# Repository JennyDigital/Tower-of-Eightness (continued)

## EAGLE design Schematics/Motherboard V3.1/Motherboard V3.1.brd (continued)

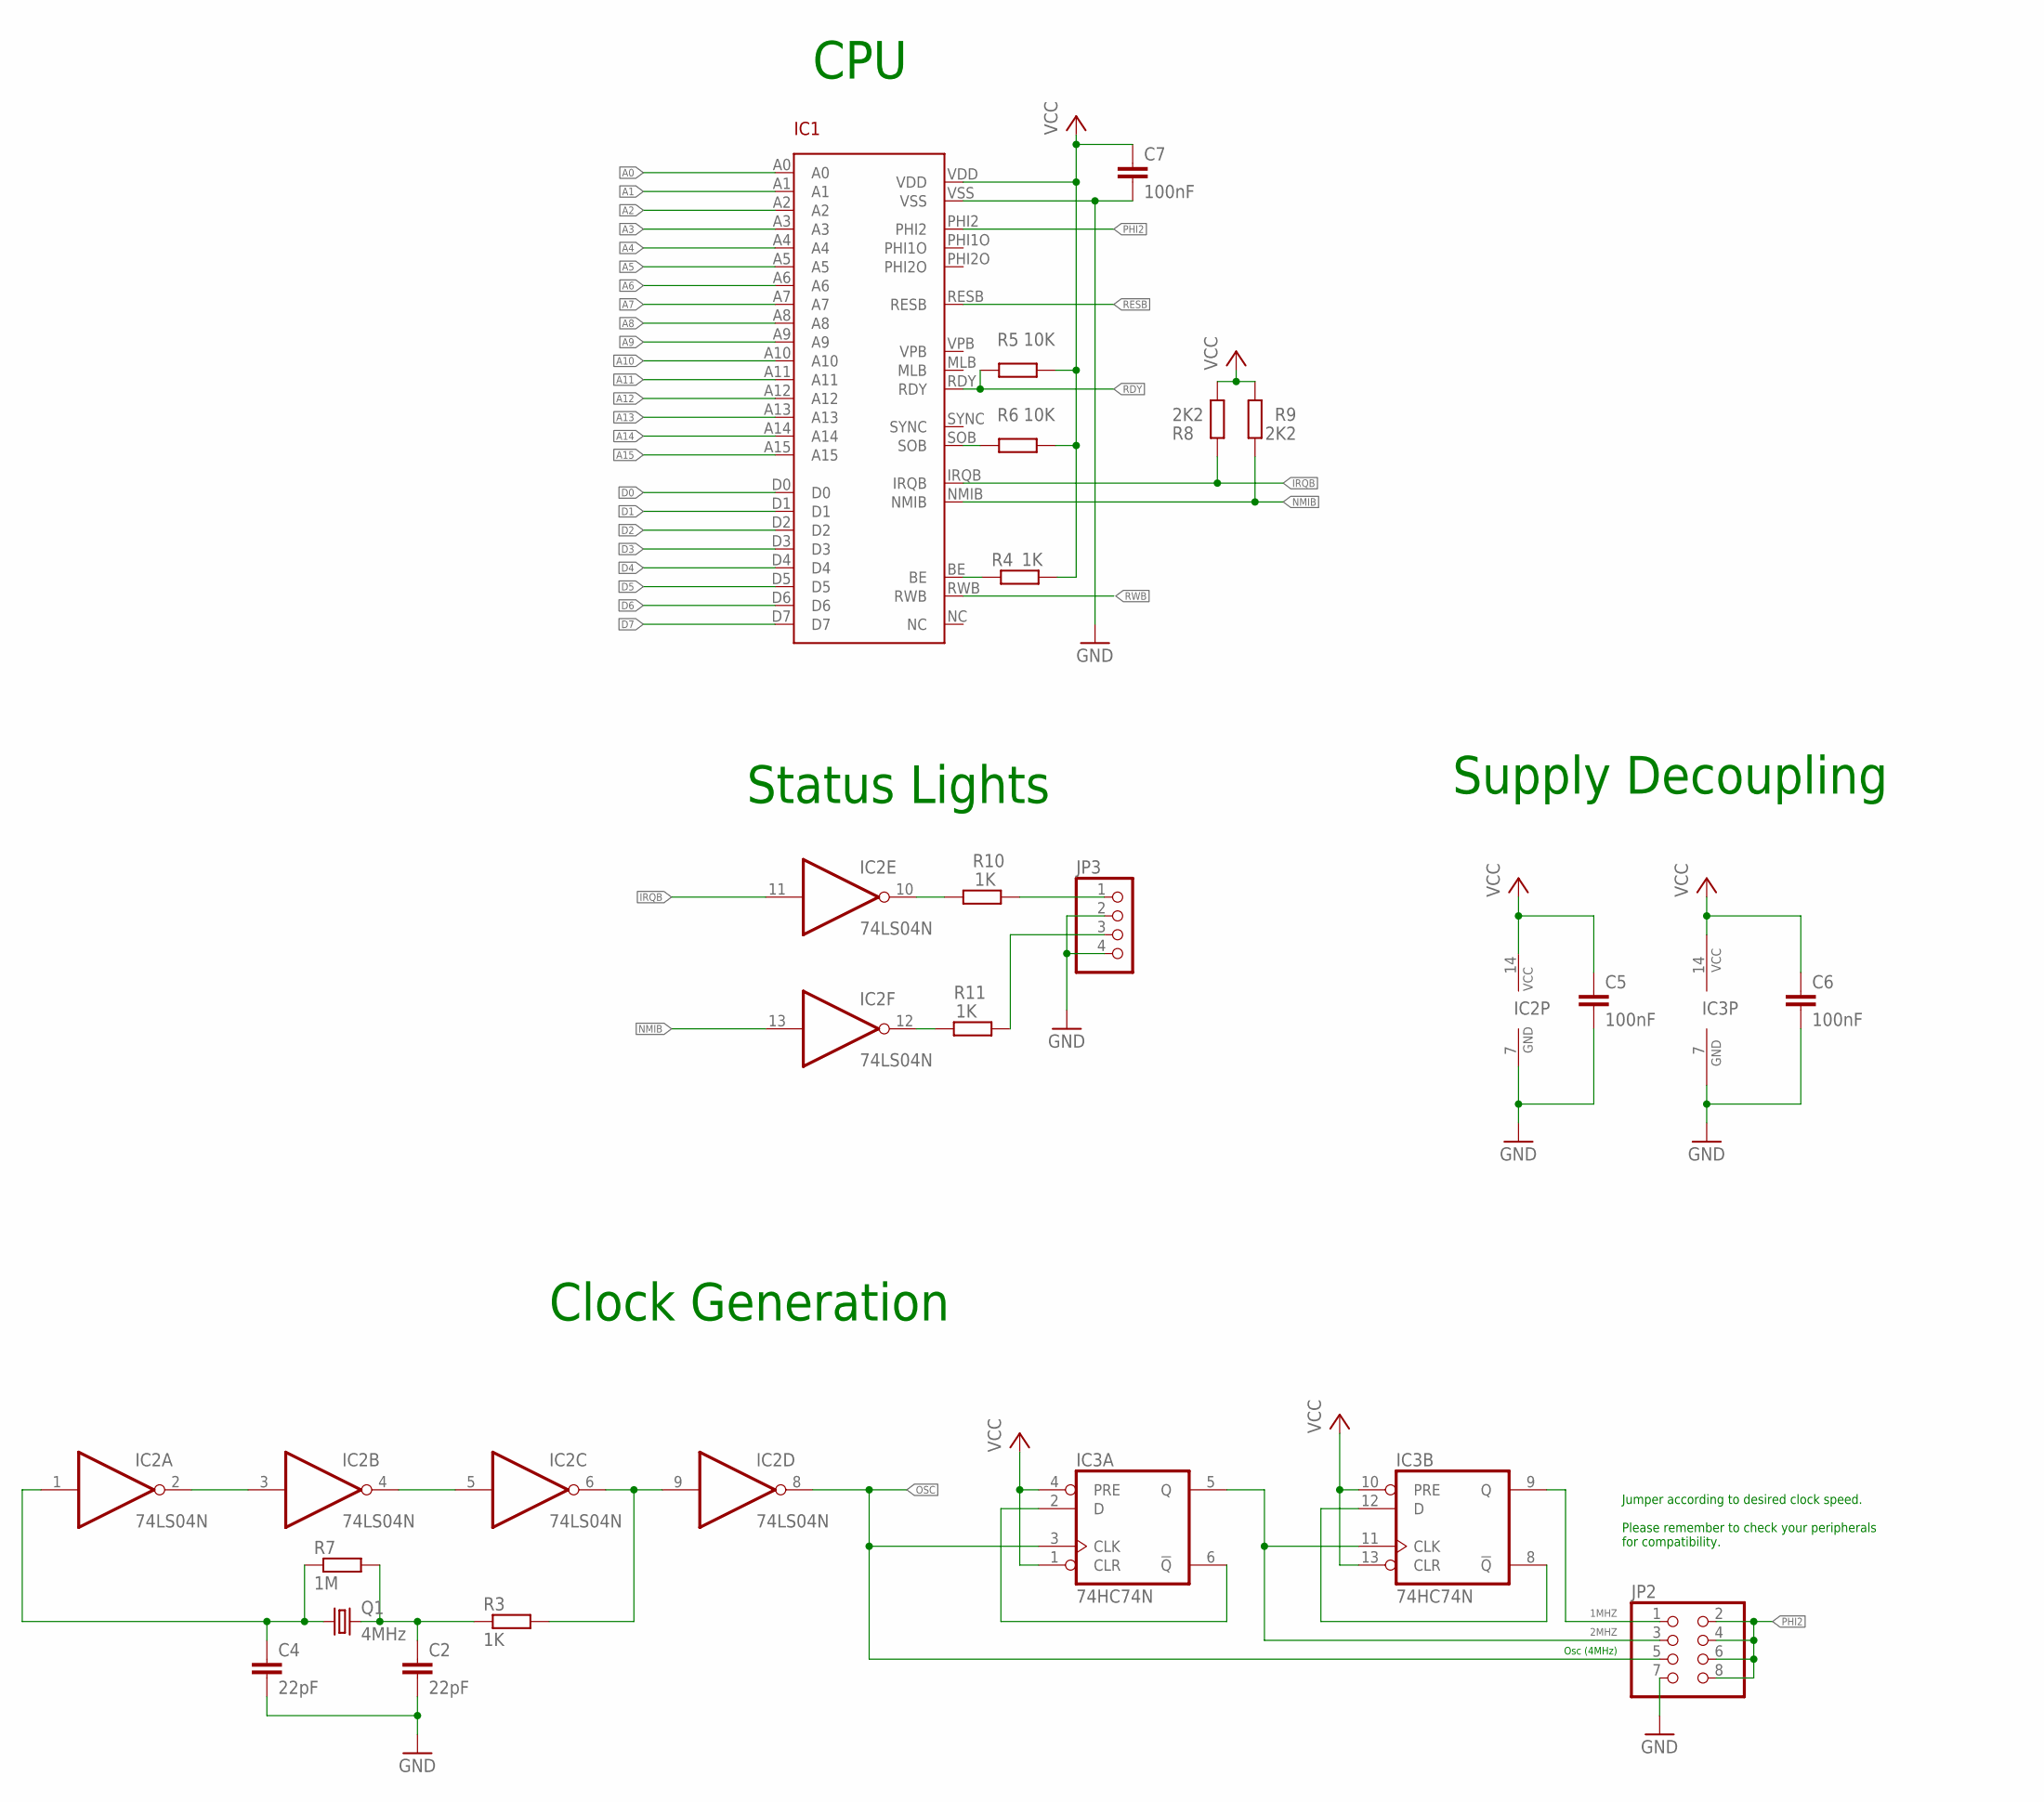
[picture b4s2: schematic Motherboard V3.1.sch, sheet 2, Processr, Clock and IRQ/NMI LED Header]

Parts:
C2, C4: 22pF; C025-025X050
C5, C6, C7: 100nF; C050-025X075
IC1: W65C02S-DIP; DIP40
IC2: 74LS04N; DIL14
IC3: 74HC74N; DIL14
JP2: PINHD-2X4; 2X04
JP3: PINHD-1X4; 1X04
Q1: 4MHz; HC49/S
R3, R10, R11: 1K; 0207/2V
R4: 1K; 0207/10
R5: 10K; 0207/2V
R6: 10K; 0207/10
R7: 1M; 0207/2V
R8, R9: 2K2; 0207/2V

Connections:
1MHZ: IC3.9 (Q), JP2.1
2MHZ: IC3.5 (Q), IC3.11 (CLK), JP2.3
A0: IC1.A0; also elsewhere on the board
A1: IC1.A1; also elsewhere on the board
A2: IC1.A2; also elsewhere on the board
A3: IC1.A3; also elsewhere on the board
A4: IC1.A4; also elsewhere on the board
A5: IC1.A5; also elsewhere on the board
A6: IC1.A6; also elsewhere on the board
A7: IC1.A7; also elsewhere on the board
A8: IC1.A8; also elsewhere on the board
A9: IC1.A9; also elsewhere on the board
A10: IC1.A10; also elsewhere on the board
A11: IC1.A11; also elsewhere on the board
A12: IC1.A12; also elsewhere on the board
A13: IC1.A13; also elsewhere on the board
A14: IC1.A14; also elsewhere on the board
A15: IC1.A15; also elsewhere on the board
D0: IC1.D0; also elsewhere on the board
D1: IC1.D1; also elsewhere on the board
D2: IC1.D2; also elsewhere on the board
D3: IC1.D3; also elsewhere on the board
D4: IC1.D4; also elsewhere on the board
D5: IC1.D5; also elsewhere on the board
D6: IC1.D6; also elsewhere on the board
D7: IC1.D7; also elsewhere on the board
GND: C2.2, C4.2, C5.2, C6.2, C7.2, IC1.VSS, IC2.7 (GND), IC3.7 (GND), JP2.7, JP3.2, JP3.4; also elsewhere on the board
IRQB: IC1.IRQB, IC2.11 (I), R8.1; also elsewhere on the board
IRQ_LED: JP3.1, R10.2
IRQ_SIG: IC2.10 (O), R10.1
unnamed: IC2.4 (O), IC2.5 (I)
unnamed: IC2.6 (O), IC2.9 (I), R3.2
unnamed: C2.1, Q1.2, R3.1, R7.2
unnamed: C4.1, IC2.1 (I), Q1.1, R7.1
unnamed: IC3.2 (D), IC3.6 (!Q)
unnamed: IC2.2 (O), IC2.3 (I)
unnamed: IC3.8 (!Q), IC3.12 (D)
unnamed: IC1.BE, R4.1
unnamed: IC1.SOB, R6.1
NMIB: IC1.NMIB, IC2.13 (I), R9.1; also elsewhere on the board
NMI_LED: JP3.3, R11.2
NMI_SIG: IC2.12 (O), R11.1
OSC: IC2.8 (O), IC3.3 (CLK), JP2.5; also elsewhere on the board
PHI2: IC1.PHI2, JP2.2, JP2.4, JP2.6, JP2.8; also elsewhere on the board
RDY: IC1.RDY, R5.1; also elsewhere on the board
RESB: IC1.RESB; also elsewhere on the board
RWB: IC1.RWB; also elsewhere on the board
VCC: C5.1, C6.1, C7.1, IC1.VDD, IC2.14 (VCC), IC3.1 (CLR), IC3.4 (PRE), IC3.10 (PRE), IC3.13 (CLR), IC3.14 (VCC), R4.2, R5.2, R6.2, R8.2, R9.2; also elsewhere on the board

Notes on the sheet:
CPU
Clock Generation
Status Lights
Supply Decoupling
Jumper according to desired clock speed. Please remember to check your peripherals for compatibility.
Osc (4MHz)

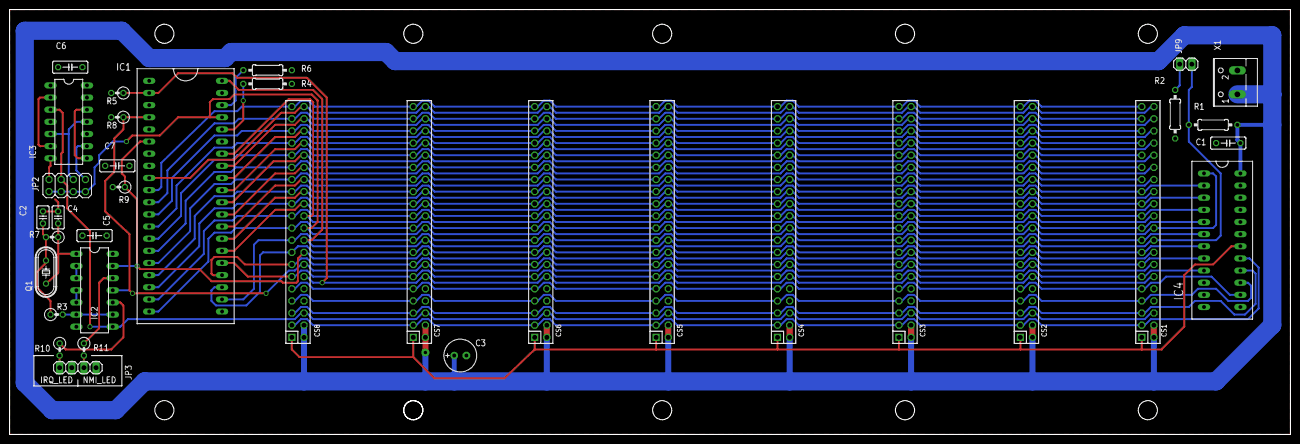
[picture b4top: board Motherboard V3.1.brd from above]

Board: 2 copper layers, 268.0 x 88.9 mm, 35 parts (0 on the bottom side), 54 nets.

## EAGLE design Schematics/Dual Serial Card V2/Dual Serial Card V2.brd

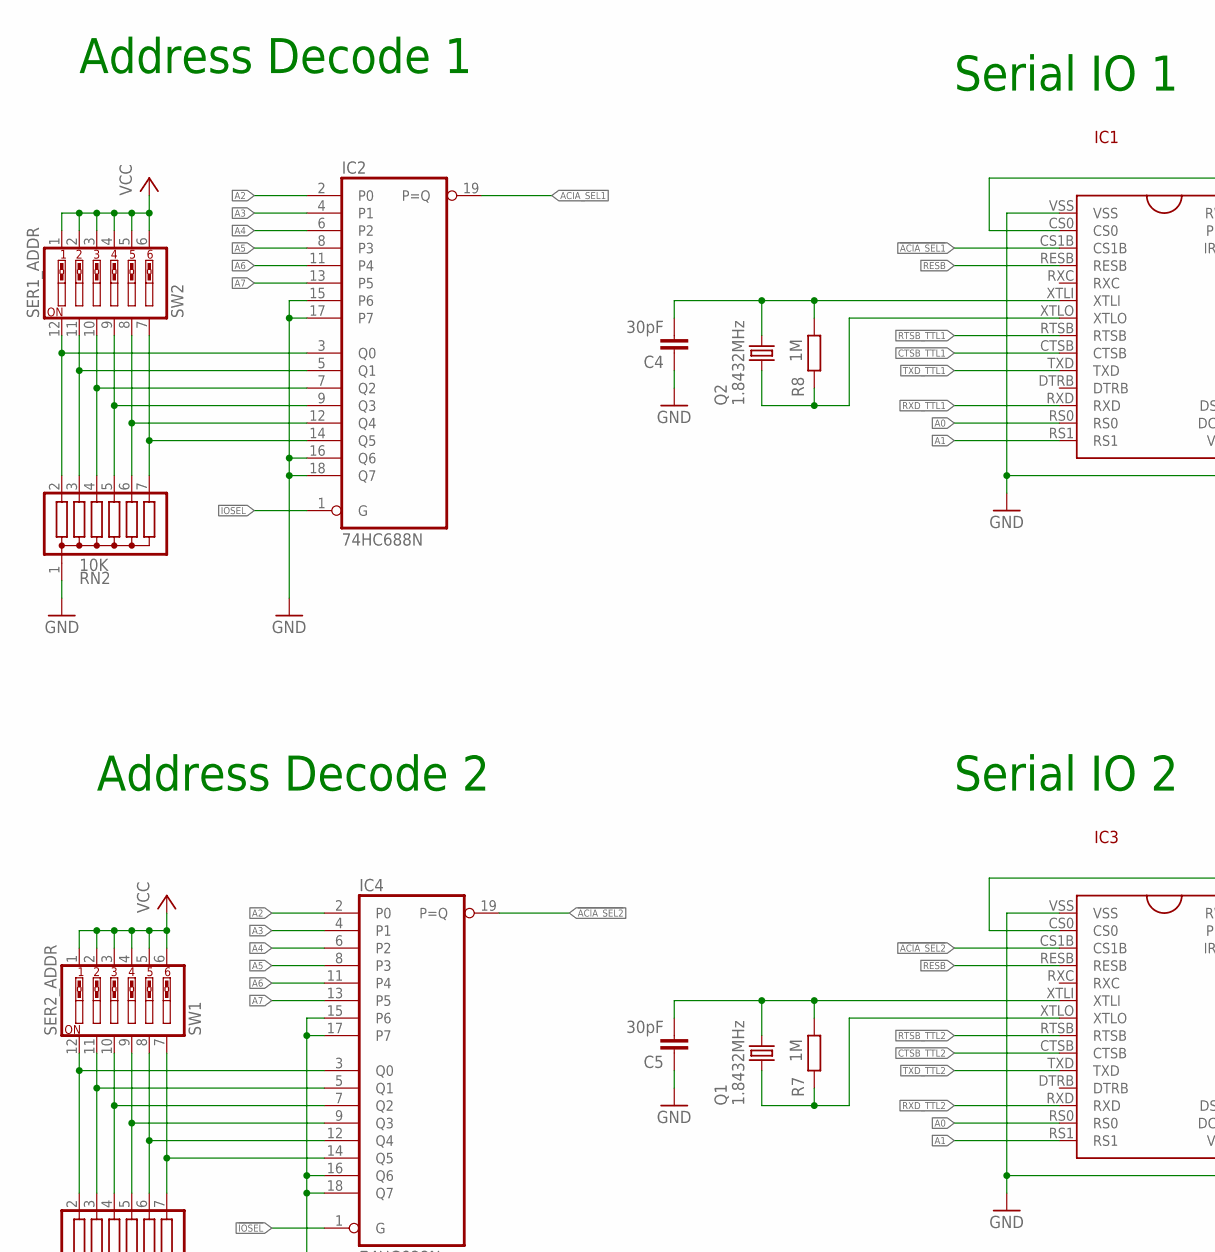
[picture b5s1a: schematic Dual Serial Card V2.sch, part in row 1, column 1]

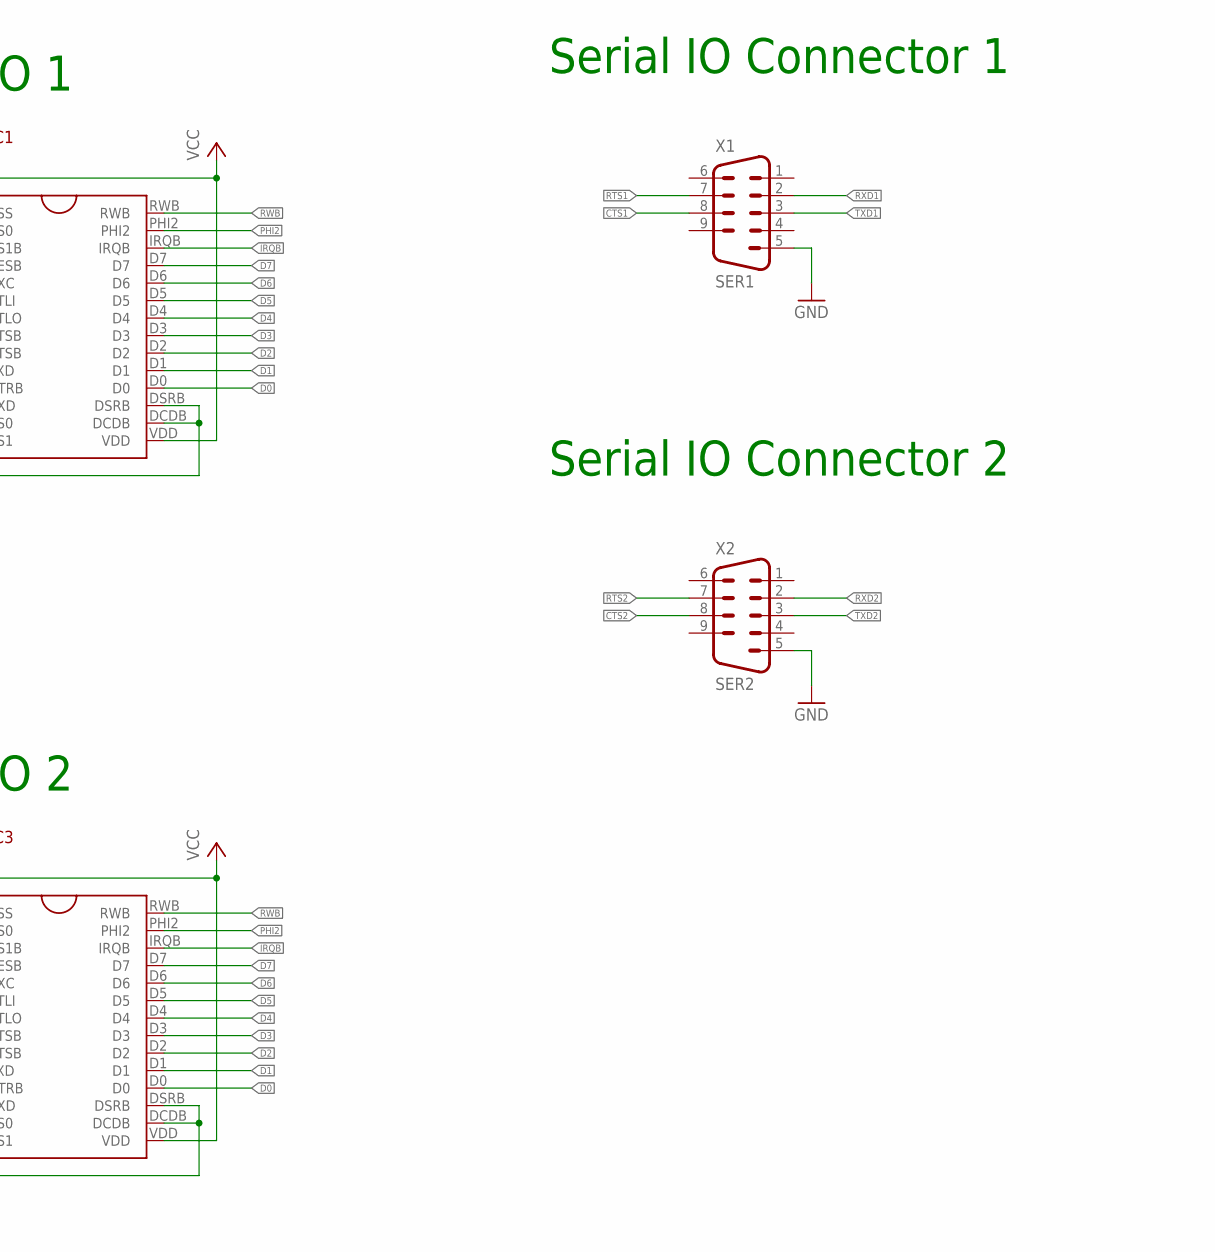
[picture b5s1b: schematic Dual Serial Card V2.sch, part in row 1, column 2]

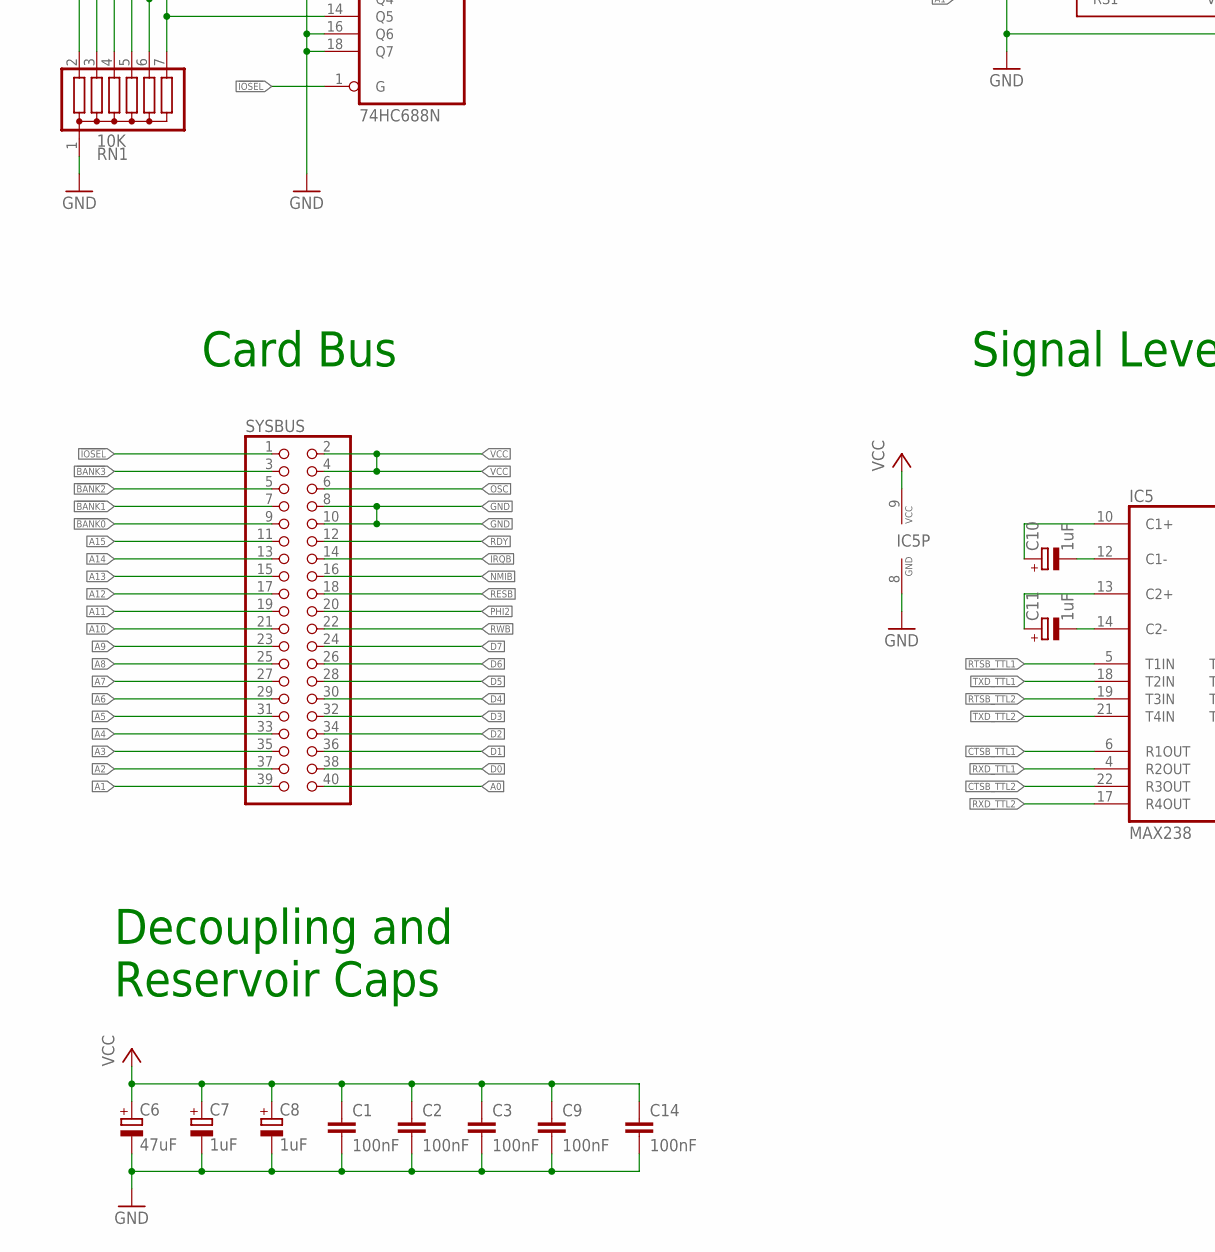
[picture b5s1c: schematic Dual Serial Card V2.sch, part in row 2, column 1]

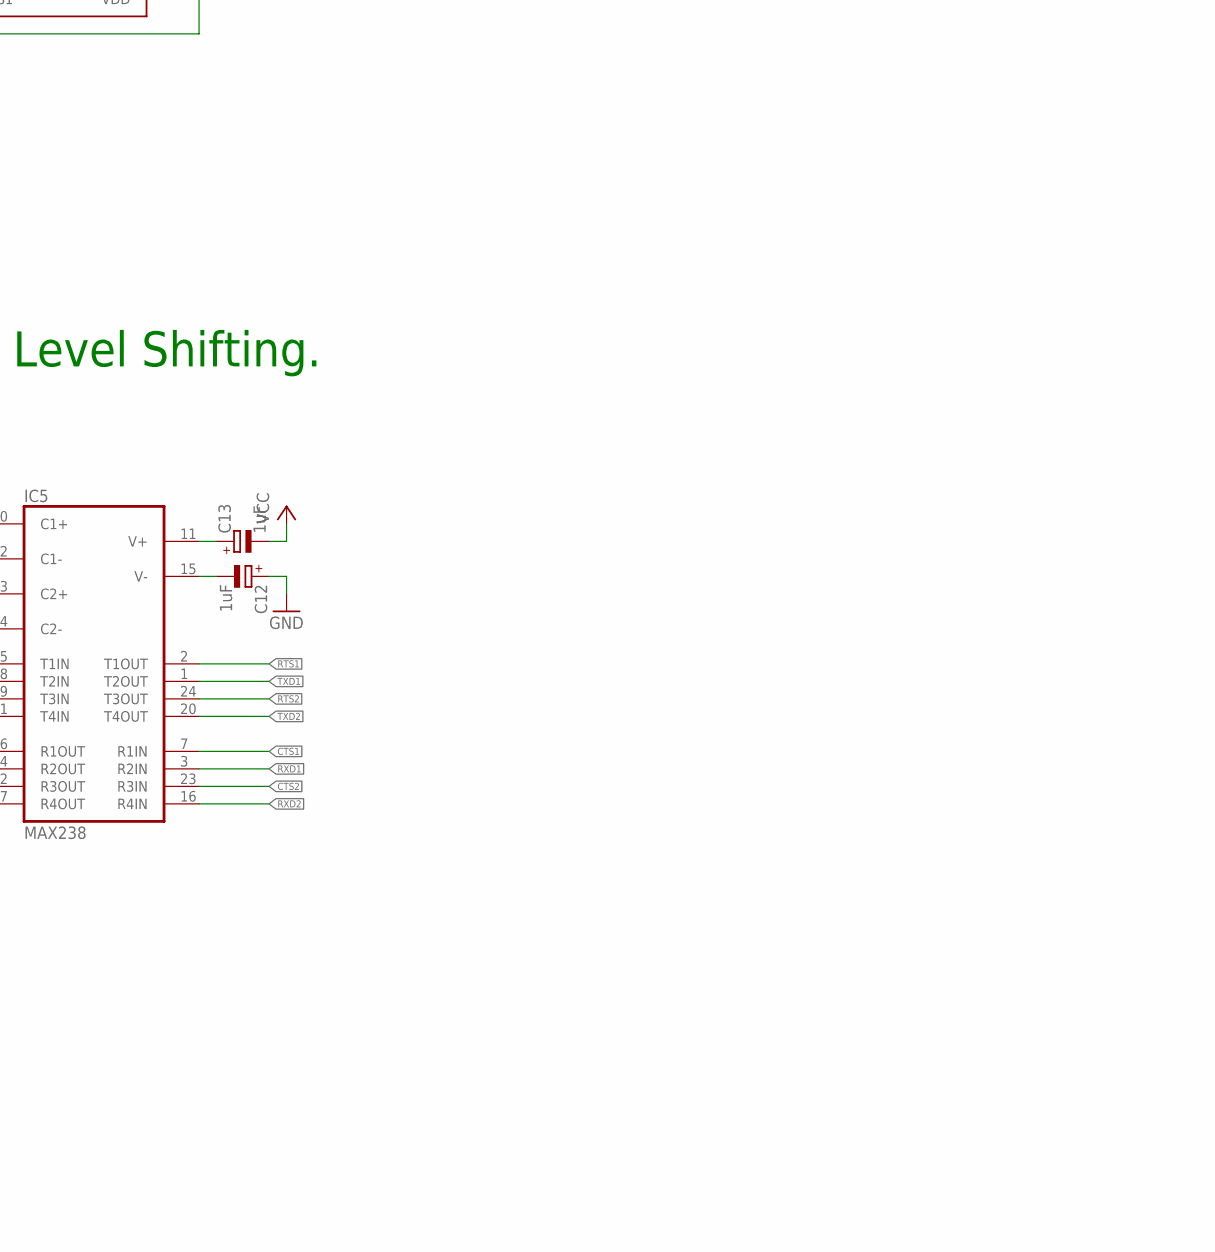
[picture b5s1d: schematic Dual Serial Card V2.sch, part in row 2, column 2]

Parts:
C1, C2, C3, C9, C14: 100nF; C025-025X050
C4, C5: 30pF; C050-025X075
C6: 47uF; E2,5-7
C7, C8, C10, C11, C12, C13: 1uF; E2,5-5
IC1, IC3: W65C51N-DIP
IC2, IC4: 74HC688N; DIL20
IC5: MAX238; DIL24-3
Q1, Q2: 1.8432MHz; HC49/S
R7, R8: 1M; 0207/2V
RN1, RN2: 10K; SIL7
SW1: SER2_ADDR; EDG-06
SW2: SER1_ADDR; EDG-06
SYSBUS: PINHD-2X20/90; 2X20/90
X1: SER1; M09HP
X2: SER2; M09HP

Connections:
!ACIA_SEL1: IC1.CS1B, IC2.19 (P=Q)
!ACIA_SEL2: IC3.CS1B, IC4.19 (P=Q)
!BANK0: SYSBUS.9
!BANK1: SYSBUS.7
!BANK2: SYSBUS.5
!BANK3: SYSBUS.3
!IOSEL: IC2.1 (G), IC4.1 (G), SYSBUS.1
A0: IC1.RS0, IC3.RS0, SYSBUS.40
A1: IC1.RS1, IC3.RS1, SYSBUS.39
A2: IC2.2 (P0), IC4.2 (P0), SYSBUS.37
A3: IC2.4 (P1), IC4.4 (P1), SYSBUS.35
A4: IC2.6 (P2), IC4.6 (P2), SYSBUS.33
A5: IC2.8 (P3), IC4.8 (P3), SYSBUS.31
A6: IC2.11 (P4), IC4.11 (P4), SYSBUS.29
A7: IC2.13 (P5), IC4.13 (P5), SYSBUS.27
A8: SYSBUS.25
A9: SYSBUS.23
A10: SYSBUS.21
A11: SYSBUS.19
A12: SYSBUS.17
A13: SYSBUS.15
A14: SYSBUS.13
A15: SYSBUS.11
CTS1: IC5.7 (R1IN), X1.8
CTS2: IC5.23 (R3IN), X2.8
CTSB_TTL1: IC1.CTSB, IC5.6 (R1OUT)
CTSB_TTL2: IC3.CTSB, IC5.22 (R3OUT)
D0: IC1.D0, IC3.D0, SYSBUS.38
D1: IC1.D1, IC3.D1, SYSBUS.36
D2: IC1.D2, IC3.D2, SYSBUS.34
D3: IC1.D3, IC3.D3, SYSBUS.32
D4: IC1.D4, IC3.D4, SYSBUS.30
D5: IC1.D5, IC3.D5, SYSBUS.28
D6: IC1.D6, IC3.D6, SYSBUS.26
D7: IC1.D7, IC3.D7, SYSBUS.24
GND: C1.2, C2.2, C3.2, C4.1, C5.1, C6.-, C7.-, C8.-, C9.2, C12.+, C14.2, IC1.DCDB, IC1.DSRB, IC1.VSS, IC2.10 (GND), IC2.15 (P6), IC2.16 (Q6), IC2.17 (P7), IC2.18 (Q7), IC3.DCDB, IC3.DSRB, IC3.VSS, IC4.10 (GND), IC4.15 (P6), IC4.16 (Q6), IC4.17 (P7), IC4.18 (Q7), IC5.8 (GND), RN1.1, RN2.1, SYSBUS.8, SYSBUS.10, X1.5, X2.5
IRQB: IC1.IRQB, IC3.IRQB, SYSBUS.14
unnamed: C5.2, IC3.XTLI, Q1.2, R7.2
unnamed: IC3.XTLO, Q1.1, R7.1
unnamed: C4.2, IC1.XTLI, Q2.2, R8.2
unnamed: IC1.XTLO, Q2.1, R8.1
unnamed: IC4.14 (Q5), RN1.7, SW1.7
unnamed: C10.-, IC5.12 (C1-)
unnamed: C10.+, IC5.10 (C1+)
unnamed: C11.-, IC5.14 (C2-)
unnamed: C11.+, IC5.13 (C2+)
unnamed: C13.+, IC5.11 (V+)
unnamed: C12.-, IC5.15 (V-)
unnamed: IC2.14 (Q5), RN2.7, SW2.7
NMIB: SYSBUS.16
OSC: SYSBUS.6
P1: IC4.12 (Q4), RN1.6, SW1.8
P2: IC4.9 (Q3), RN1.5, SW1.9
P3: IC2.12 (Q4), RN2.6, SW2.8
P4: IC2.9 (Q3), RN2.5, SW2.9
P5: IC2.7 (Q2), RN2.4, SW2.10
P6: IC2.5 (Q1), RN2.3, SW2.11
P8: IC4.7 (Q2), RN1.4, SW1.10
P9: IC4.5 (Q1), RN1.3, SW1.11
PHI2: IC1.PHI2, IC3.PHI2, SYSBUS.20
RDY: SYSBUS.12
RESB: IC1.RESB, IC3.RESB, SYSBUS.18
RTS1: IC5.2 (T1OUT), X1.7
RTS2: IC5.24 (T3OUT), X2.7
RTSB_TTL1: IC1.RTSB, IC5.5 (T1IN)
RTSB_TTL2: IC3.RTSB, IC5.19 (T3IN)
RWB: IC1.RWB, IC3.RWB, SYSBUS.22
RXD1: IC5.3 (R2IN), X1.2
RXD2: IC5.16 (R4IN), X2.2
RXD_TTL1: IC1.RXD, IC5.4 (R2OUT)
RXD_TTL2: IC3.RXD, IC5.17 (R4OUT)
S1_A2: IC2.3 (Q0), RN2.2, SW2.12
S2_A2: IC4.3 (Q0), RN1.2, SW1.12
TXD1: IC5.1 (T2OUT), X1.3
TXD2: IC5.20 (T4OUT), X2.3
TXD_TTL1: IC1.TXD, IC5.18 (T2IN)
TXD_TTL2: IC3.TXD, IC5.21 (T4IN)
VCC: C1.1, C2.1, C3.1, C6.+, C7.+, C8.+, C9.1, C13.-, C14.1, IC1.CS0, IC1.VDD, IC2.20 (VCC), IC3.CS0, IC3.VDD, IC4.20 (VCC), IC5.9 (VCC), SW1.1, SW1.2, SW1.3, SW1.4, SW1.5, SW1.6, SW2.1, SW2.2, SW2.3, SW2.4, SW2.5, SW2.6, SYSBUS.2, SYSBUS.4

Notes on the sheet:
Card Bus
Decoupling and Reservoir Caps
Address Decode 1
Serial IO 2
Serial IO Connector 2
Serial IO 1
Signal Level Shifting.
Serial IO Connector 1
Address Decode 2

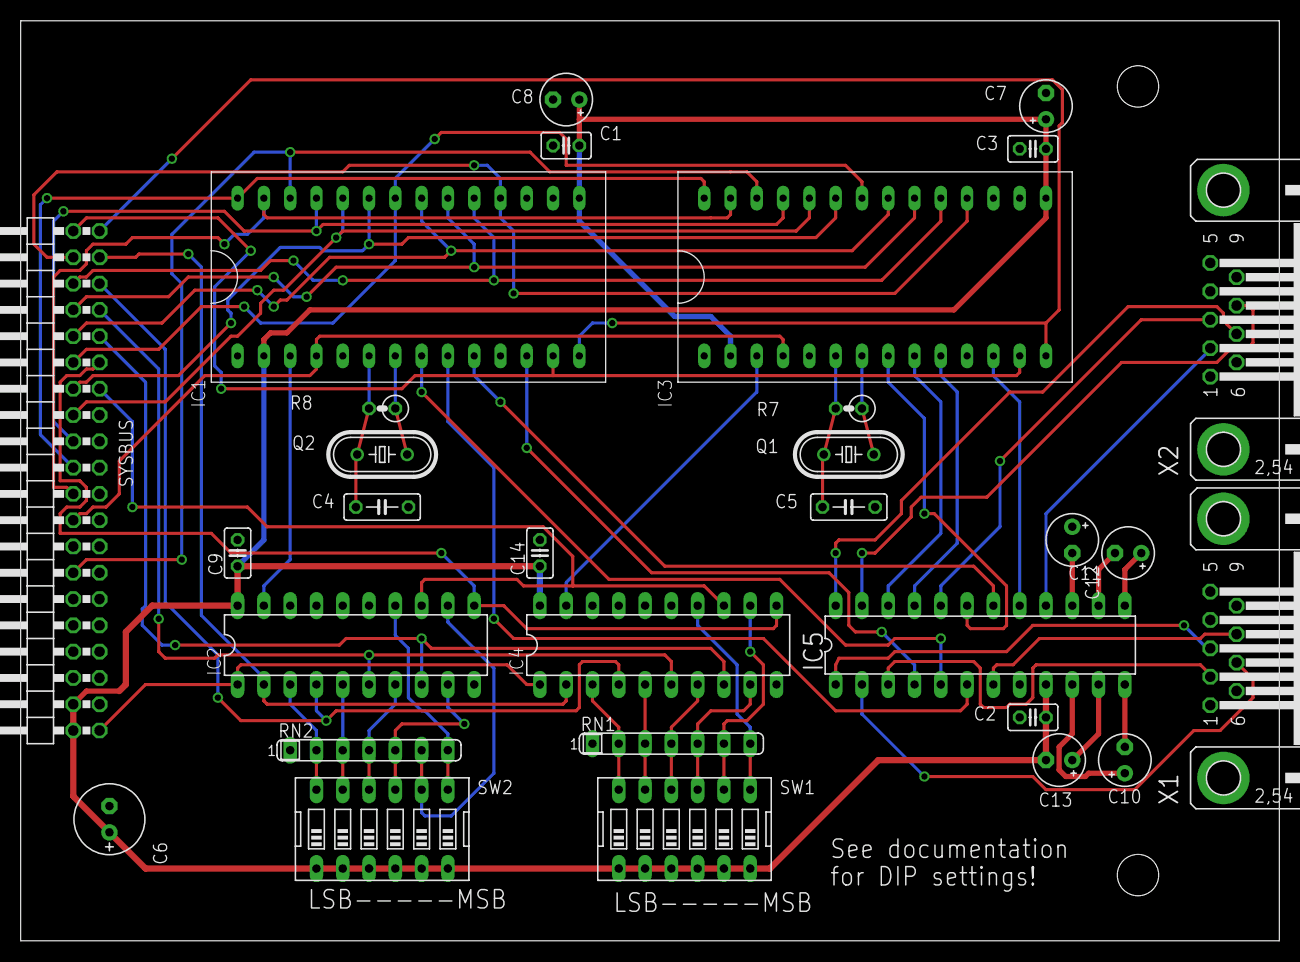
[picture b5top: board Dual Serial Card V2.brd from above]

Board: 2 copper layers, 121.6 x 88.9 mm, 30 parts (0 on the bottom side), 63 nets.

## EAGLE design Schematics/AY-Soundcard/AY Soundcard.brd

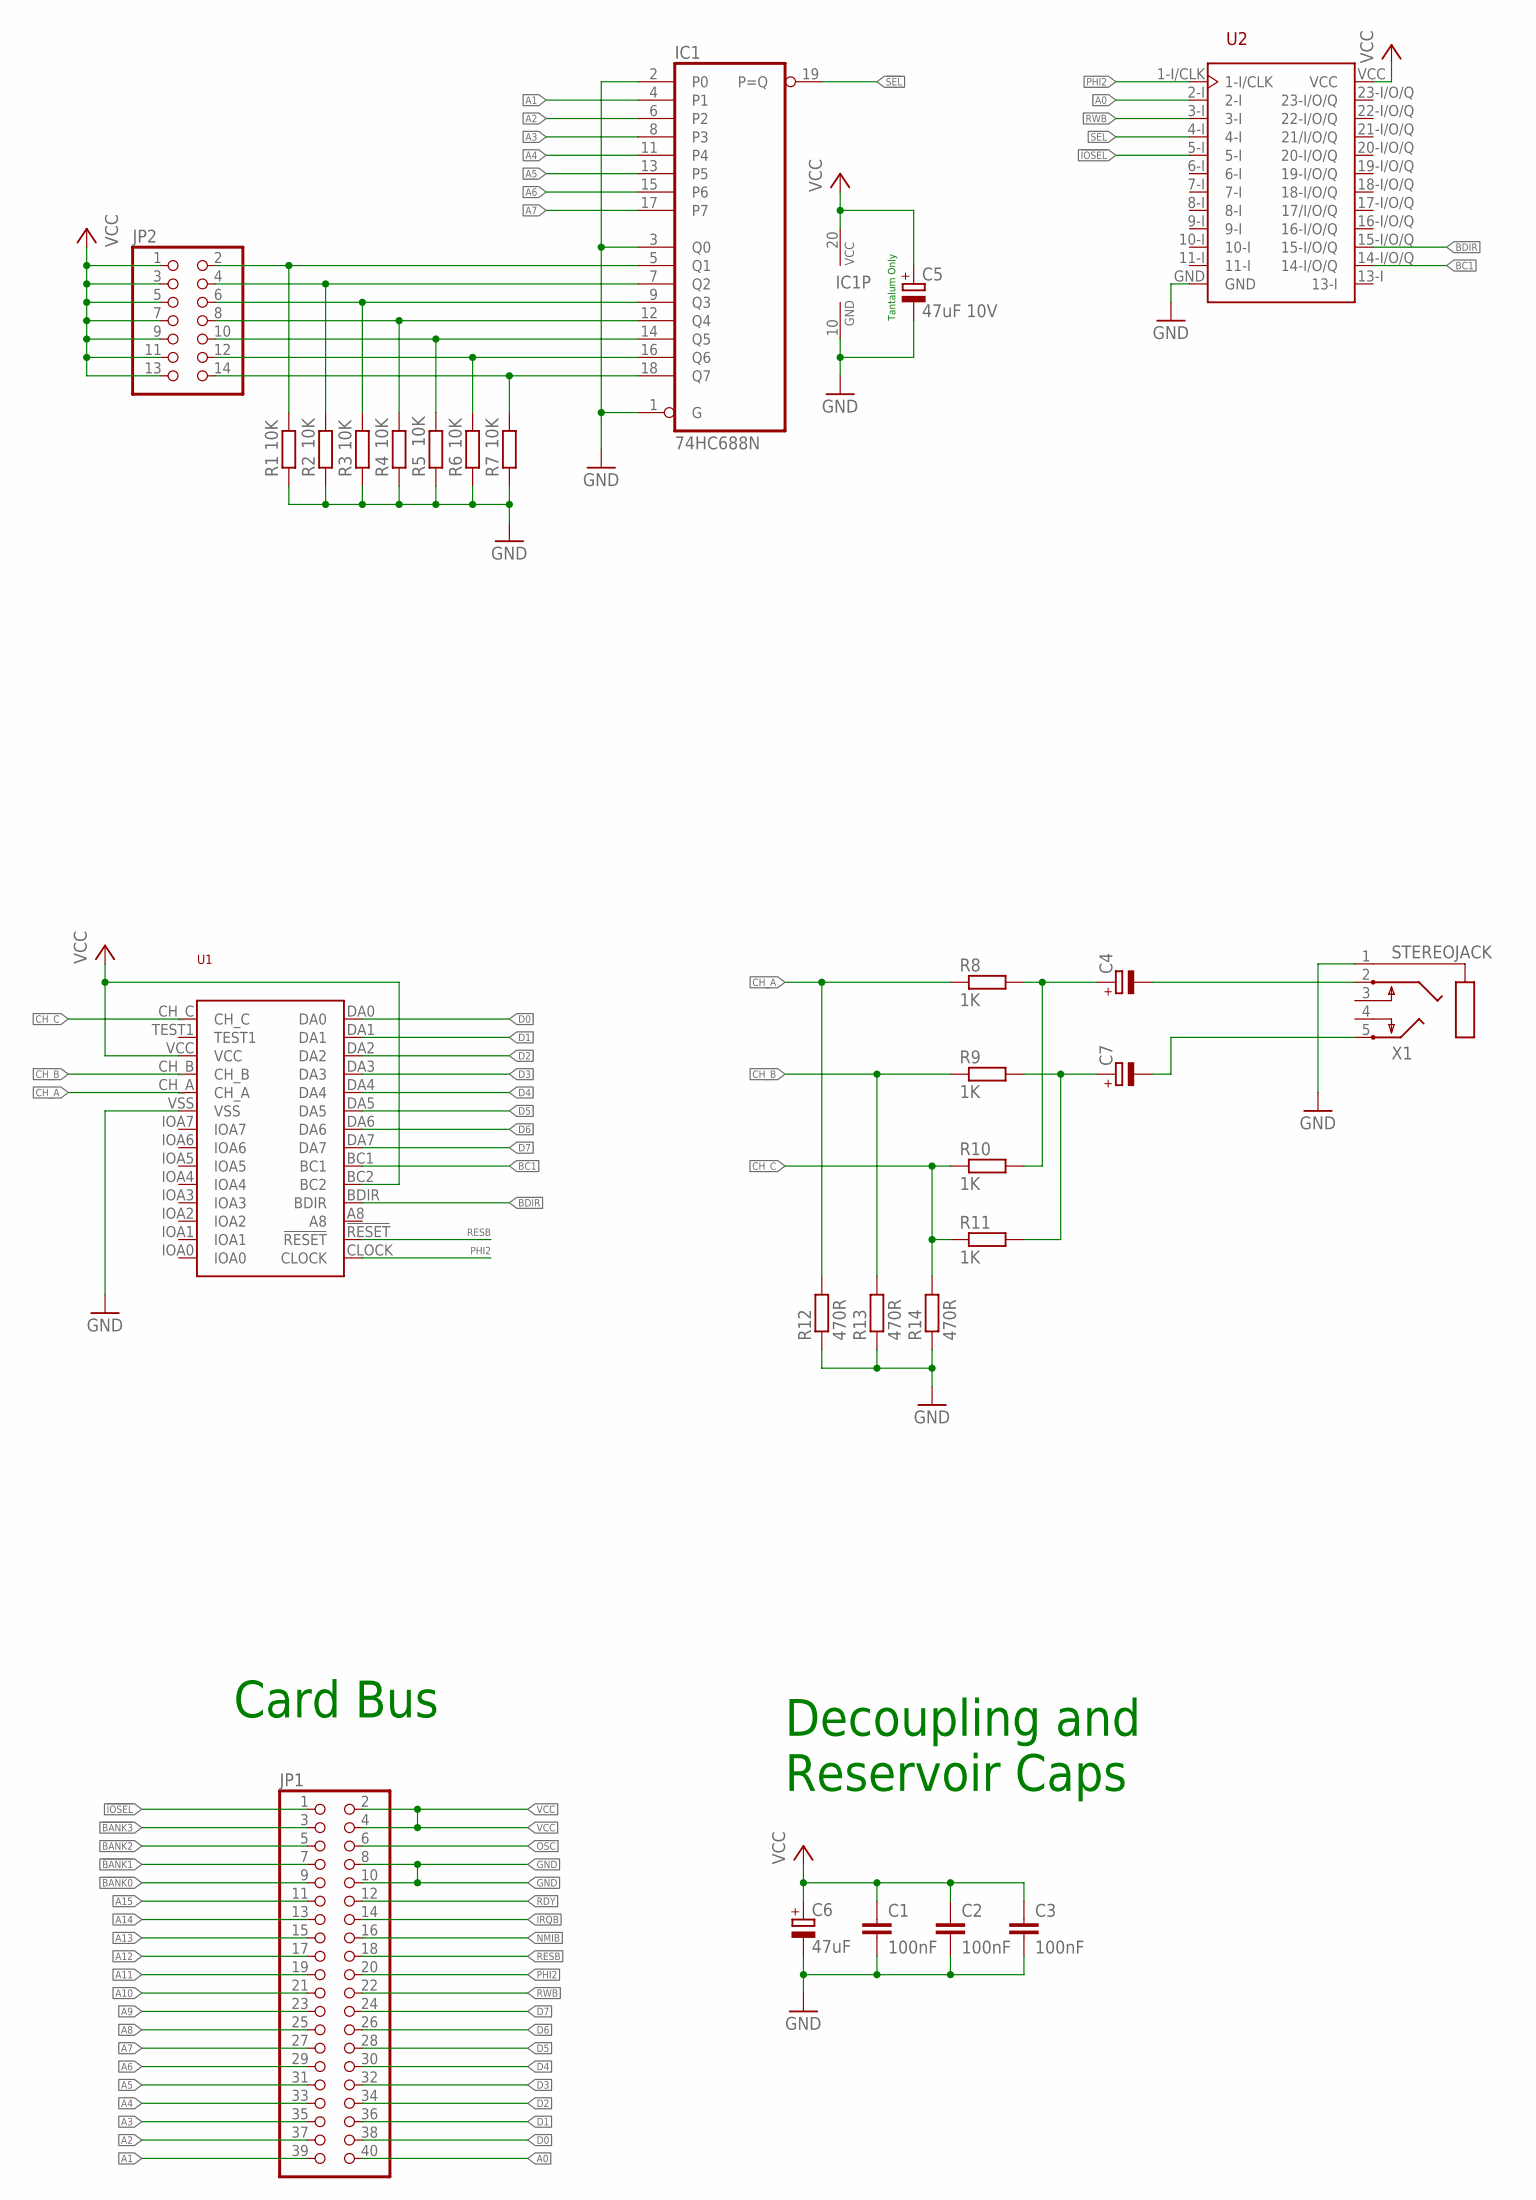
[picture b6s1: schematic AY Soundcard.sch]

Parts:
C1, C2, C3: 100nF; C050-025X075
C4, C7: CPOL-EUE2-5; E2-5
C5: 47uF 10V; E5-6
C6: 47uF; E2,5-7
IC1: 74HC688N; DIL20
JP1: PINHD-2X20/90; 2X20/90
JP2: PINHD-2X7; 2X07
R1, R2, R3, R4, R5, R6, R7: 10K; 0207/2V
R8, R9, R10, R11: 1K; 0207/2V
R12: 470R; 0207/2V
R13, R14: 470R; 0207/10
U1: AY-3-8912-DIP; DIP
U2: GAL22V10D-DIP; DIP24
X1: STEREOJACK; STX3100

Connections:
!BANK0: JP1.9
!BANK1: JP1.7
!BANK2: JP1.5
!BANK3: JP1.3
!IOSEL: JP1.1, U2.5-I
!SEL: IC1.19 (P=Q), U2.4-I
A0: JP1.40, U2.2-I
A1: IC1.4 (P1), JP1.39
A2: IC1.6 (P2), JP1.37
A3: IC1.8 (P3), JP1.35
A4: IC1.11 (P4), JP1.33
A5: IC1.13 (P5), JP1.31
A6: IC1.15 (P6), JP1.29
A7: IC1.17 (P7), JP1.27
A8: JP1.25
A9: JP1.23
A10: JP1.21
A11: JP1.19
A12: JP1.17
A13: JP1.15
A14: JP1.13
A15: JP1.11
BC1: U1.BC1, U2.14-I/O/Q
BDIR: U1.BDIR, U2.15-I/O/Q
CH_A: R8.1, R12.2, U1.CH_A
CH_B: R9.1, R13.2, U1.CH_B
CH_C: R10.1, R11.1, R14.2, U1.CH_C
D0: JP1.38, U1.DA0
D1: JP1.36, U1.DA1
D2: JP1.34, U1.DA2
D3: JP1.32, U1.DA3
D4: JP1.30, U1.DA4
D5: JP1.28, U1.DA5
D6: JP1.26, U1.DA6
D7: JP1.24, U1.DA7
GND: C1.2, C2.2, C3.2, C5.-, C6.-, IC1.1 (G), IC1.2 (P0), IC1.3 (Q0), IC1.10 (GND), JP1.8, JP1.10, R1.1, R2.1, R3.1, R4.1, R5.1, R6.1, R7.1, R12.1, R13.1, R14.1, U1.VSS, U2.GND, X1.1
IRQB: JP1.14
unnamed: C4.+, R8.2, R10.2
unnamed: C7.+, R9.2, R11.2
unnamed: C4.-, X1.2
unnamed: C7.-, X1.5
unnamed: IC1.5 (Q1), JP2.2, R1.2
unnamed: IC1.7 (Q2), JP2.4, R2.2
unnamed: IC1.9 (Q3), JP2.6, R3.2
unnamed: IC1.12 (Q4), JP2.8, R4.2
unnamed: IC1.14 (Q5), JP2.10, R5.2
unnamed: IC1.16 (Q6), JP2.12, R6.2
unnamed: IC1.18 (Q7), JP2.14, R7.2
NMIB: JP1.16
OSC: JP1.6
PHI2: JP1.20, U1.CLOCK, U2.1-I/CLK
RDY: JP1.12
RESB: JP1.18, U1.!RESET
RWB: JP1.22, U2.3-I
VCC: C1.1, C2.1, C3.1, C5.+, C6.+, IC1.20 (VCC), JP1.2, JP1.4, JP2.1, JP2.3, JP2.5, JP2.7, JP2.9, JP2.11, JP2.13, U1.BC2, U1.VCC, U2.VCC

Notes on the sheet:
Card Bus
Decoupling and Reservoir Caps
Tantalum Only

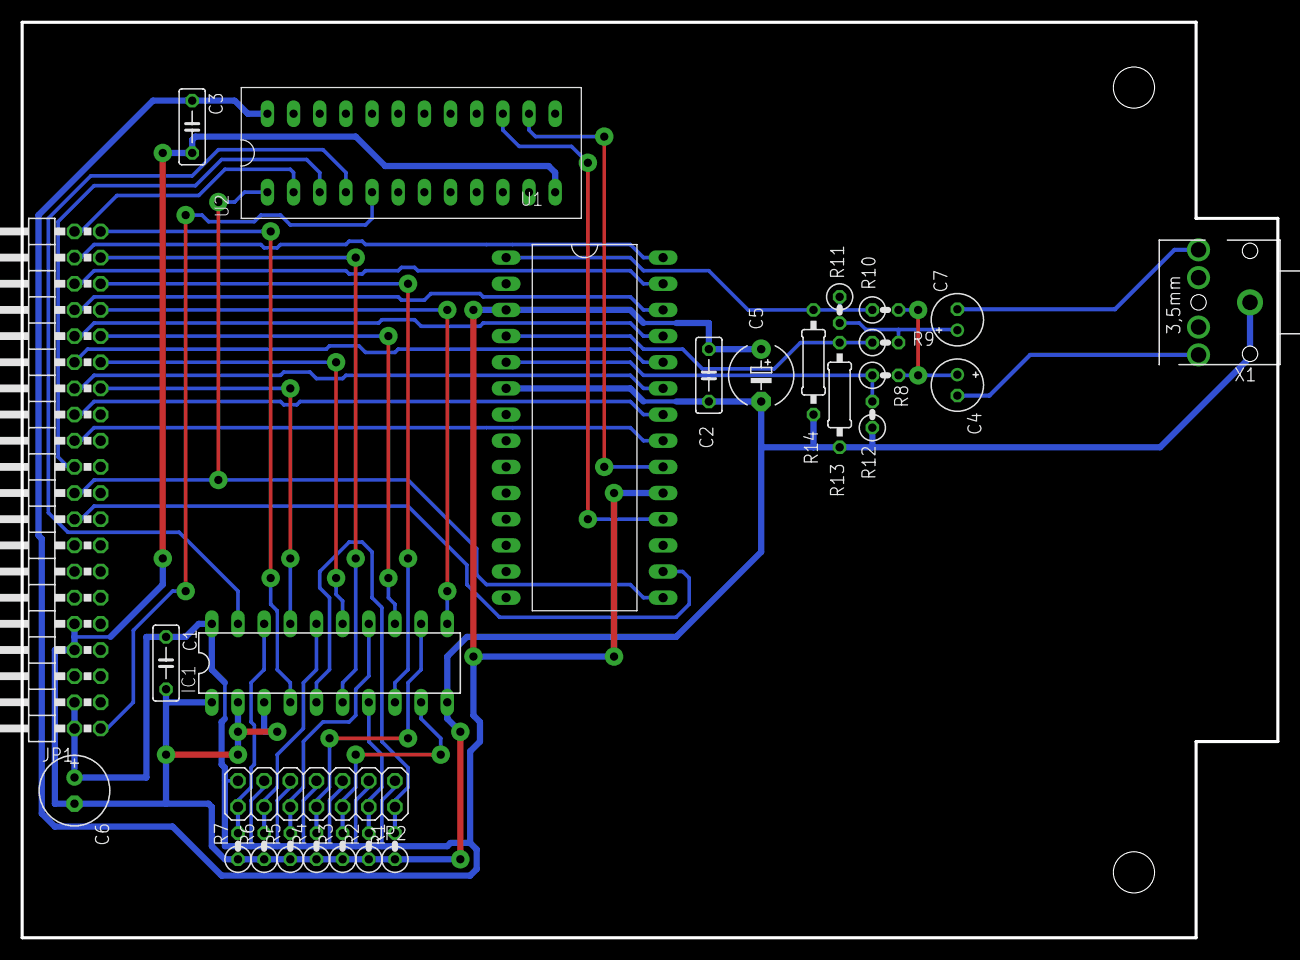
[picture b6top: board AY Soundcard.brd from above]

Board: 2 copper layers, 121.9 x 88.9 mm, 27 parts (0 on the bottom side), 39 nets.
